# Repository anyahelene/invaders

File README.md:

# invaders
##### A hand-held retro console based on the ATmega328P chip

## Features
* [ATmega328P](https://www.microchip.com/wwwproducts/en/ATMEGA328P) as the CPU, with
   * 16 MHz clock
   * 32 KiB flash memory for programs
   * 2 KiB static ram
   * 1 KiB EEPROM
* Choice of one of three OLED displays:
   * 2.42" monochrome 128x64 OLED with SPI interface, e.g., [this one from DIYMORE](https://www.diymore.cc/collections/display-module/products/2-42-inch-12864-oled-display-module-iic-i2c-spi-serial-for-arduino-c51-stm32-green-white-blue-yellow)
   * 1.5" color 128x128 OLED with SPI interface, e.g., [this one from Waveshare](https://www.waveshare.com/1.5inch-RGB-OLED-Module.htm)
   * 1.3" monochrome 128x64 OLED with I2C interface, found as infinite clones such as [this one from Luxorparts](https://www.kjell.com/no/produkter/elektro-og-verktoy/elektronikk/optokomponenter/led-lcd-skjermer/luxorparts-grafisk-oled-skjerm-128-x-64-piksler-1-3--p87946)
   * The board has pin headers and mounting holes for these three displays, but other display sizes might fit, and different pinouts might be accommodated by wires
   * The above displays are available from Ebay ($2.50 for a small display, up to ~$18 for large/color), and similar displays can be found at [Adafruit](https://adafruit.com/), [Sparkfun](https://sparkfun.com/) or your local electronics store
* Four directional buttons on the left-hand side
* [Thumbstick (PSP1000 replacement)](https://www.adafruit.com/product/444) *or* two buttons on the right-hand side
* Two trigger buttons on the top edge
* Reset button on the bottom side
* Space for 2xAAA batteries + also a JST-PH battery connector (as seen on the micro:bit)
* Micro USB power connector
* 6 pin AVR ICSP header for programming
* Space for a tiny speaker/buzzer
* Power led + two controllable leds
* Four M2 mounting holes

## (Soft|Firm)ware
* TBD

## Circuit board
* [KiCad](http://www.kicad-pcb.org/) files for the board can be found in the [pcb/](pcb/) subdirectory.
* You also need the symbols and footprints from https://github.com/anyahelene/a-symbols
* Alternatively, the board can be manufactured directly from the Gerber files in [pcb/fab/](pcb/fab/).
* An [interactive BOM](https://htmlpreview.github.io/?https://github.com/anyahelene/invaders/blob/master/pcb/bom/ibom.html) is available in [pcb/bom/](pcb/bom/)

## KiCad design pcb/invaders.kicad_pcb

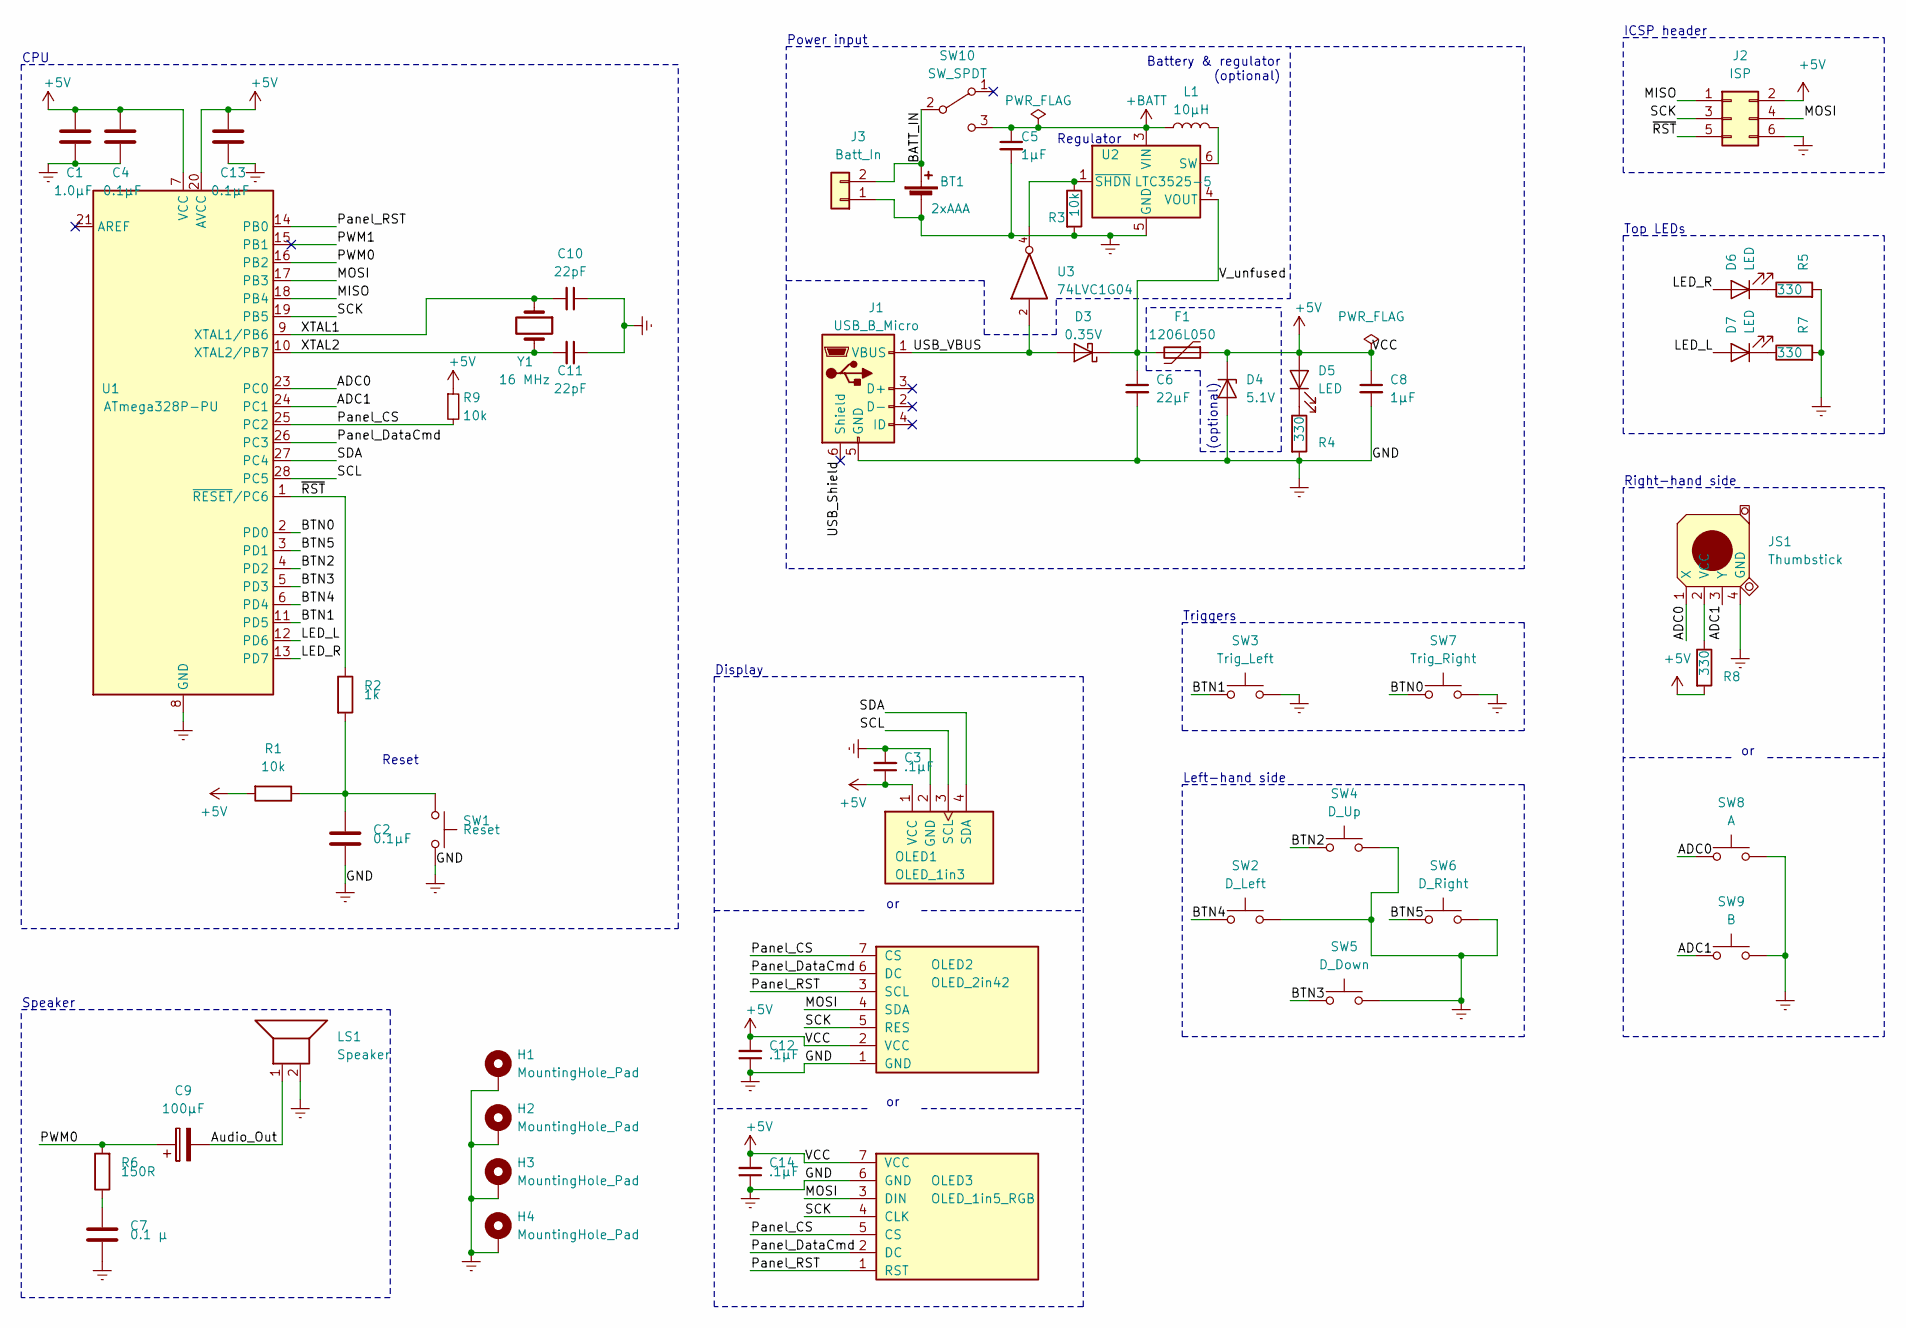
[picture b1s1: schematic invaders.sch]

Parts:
BT1: 2xAAA; BatteryHolder_Keystone_2468_2xAAA; Part Keystone 2468
C1: 1.0µF; C_1206_3216Metric_Pad1.42x1.75mm_HandSolder
C2, C4, C13: 0.1µF; C_0805_2012Metric_Pad1.15x1.40mm_HandSolder
C3, C12, C14: .1µF; C_0805_2012Metric_Pad1.15x1.40mm_HandSolder
C5, C8: 1µF; C_1206_3216Metric_Pad1.42x1.75mm_HandSolder
C6: 22µF; C_1206_3216Metric_Pad1.42x1.75mm_HandSolder; Part Taiyo LMK316ABJ226ML-T
C7: 0.1 µ; C_0805_2012Metric_Pad1.15x1.40mm_HandSolder
C9: 100µF; CP_Radial_D6.3mm_P2.50mm
C10, C11: 22pF; C_0805_2012Metric_Pad1.15x1.40mm_HandSolder
D3: 0.35V; D_SOD-123F; Part Rohm RSX101MM-30TR
D4: 5.1V; D_DO-41_SOD81_P7.62mm_Horizontal; Part RND 1N4733A
D5, D6, D7: LED; LED_1206_3216Metric_Pad1.42x1.75mm_HandSolder
F1: 1206L050; Fuse_1206_3216Metric_Pad1.42x1.75mm_HandSolder
H1, H2, H3, H4: MountingHole_Pad; MountingHole_2.2mm_M2_Pad_Via
J1: USB_B_Micro; USB_Micro-B_Molex-105017-0001; Part Molex 105017
J2: ISP; PinHeader_2x03_P2.54mm_Vertical
J3: Batt_In; JST_PH_S2B-PH-K_1x02_P2.00mm_Horizontal
JS1: Thumbstick; psp_thumbstick; Part PSP1000 thumbstick
L1: 10µH; L_1210_3225Metric_Pad1.42x2.65mm_HandSolder; Part Murata DFE322512C 1277A
LS1: Speaker; Buzzer_12x9.5RM7.6
OLED1: OLED_1in3; OLED_1in3_i2c
OLED2: OLED_2in42; OLED_2in42_spi_i2c
OLED3: OLED_1in5_RGB; OLED_1in5_spi_rgb
R1, R3, R9: 10k; R_1206_3216Metric_Pad1.42x1.75mm_HandSolder
R2: 1k; R_1206_3216Metric_Pad1.42x1.75mm_HandSolder
R4, R5, R7, R8: 330; R_1206_3216Metric_Pad1.42x1.75mm_HandSolder
R6: 150R; R_1206_3216Metric_Pad1.42x1.75mm_HandSolder
SW1: Reset; SW_PUSH_6mm; Part 6x6mm tactile, e.g. ALPS SKHHAMA010
SW2: D_Left; SW_PUSH_6mm; Part 6x6mm tactile, e.g. ALPS SKHHAMA010
SW3: Trig_Left; SW_Tactile_SPST_Angled_PTS645Vx58-2LFS; Part 6mm angled tactile, e.g. C&K PTS645VM58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
SW4: D_Up; SW_PUSH_6mm; Part 6x6mm tactile, e.g. ALPS SKHHAMA010
SW5: D_Down; SW_PUSH_6mm; Part 6x6mm tactile, e.g. ALPS SKHHAMA010
SW6: D_Right; SW_PUSH_6mm; Part 6x6mm tactile, e.g. ALPS SKHHAMA010
SW7: Trig_Right; SW_Tactile_SPST_Angled_PTS645Vx58-2LFS; Part 6mm angled tactile, e.g. C&K PTS645VM58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
SW8: A; SW_PUSH_6mm; Part 6x6mm tactile, e.g. ALPS SKHHAMA010
SW9: B; SW_PUSH_6mm; Part 6x6mm tactile, e.g. ALPS SKHHAMA010
SW10: SW_SPDT; SW_E-Switch_EG1224_SPDT_Angled
U1: ATmega328P-PU; DIP-28_W7.62mm_Socket
U2: LTC3525-5; SOT-363_SC-70-6
U3: 74LVC1G04; SOT-23-5_HandSoldering
Y1: 16 MHz; Crystal_HC49-4H_Vertical

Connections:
+5V: C1.1, C3.1, C4.1, C8.1, C12.2, C13.1, C14.2, D4.1 (K), D5.2 (A), F1.1, J2.2, OLED1.1 (VCC), OLED2.2 (VCC), OLED3.7 (VCC), R1.2, R8.2, R9.1, U1.7 (VCC), U1.20 (AVCC), U3.5 (VCC)
+BATT: C5.1, L1.1, SW10.3 (C), U2.3 (VIN)
/ADC0: JS1.1 (X), SW8.1, U1.23 (PC0)
/ADC1: JS1.3 (Y), SW9.1, U1.24 (PC1)
/Audio_Out: C9.2, LS1.1
/BATT_IN: BT1.1 (+), J3.2, SW10.2 (B)
/BTN0: SW7.1, U1.2 (PD0)
/BTN1: SW3.1, U1.11 (PD5)
/BTN2: SW4.1, U1.4 (PD2)
/BTN3: SW5.1, U1.5 (PD3)
/BTN4: SW2.1, U1.6 (PD4)
/BTN5: SW6.1, U1.3 (PD1)
/LED_L: D7.2 (A), U1.12 (PD6)
/LED_R: D6.2 (A), U1.13 (PD7)
/MISO: J2.1, U1.18 (PB4)
/MOSI: J2.4, OLED2.4 (SDA), OLED3.3 (DIN), U1.17 (PB3)
/PWM0: C9.1, R6.2, U1.16 (PB2)
/Panel_CS: OLED2.7 (CS), OLED3.5 (CS), R9.2, U1.25 (PC2)
/Panel_DataCmd: OLED2.6 (DC), OLED3.2 (DC), U1.26 (PC3)
/Panel_RST: OLED2.3 (SCL), OLED3.1 (RST), U1.14 (PB0)
/SCK: J2.3, OLED2.5 (RES), OLED3.4 (CLK), U1.19 (PB5)
/SCL: OLED1.3 (SCL), U1.28 (PC5)
/SDA: OLED1.4 (SDA), U1.27 (PC4)
/USB_Shield: J1.6 (Shield)
/USB_VBUS: D3.2 (A), J1.1 (VBUS), U3.2
/V_unfused: C6.1, D3.1 (K), F1.2, U2.4 (VOUT)
/XTAL1: C10.2, U1.9 (XTAL1/PB6), Y1.1
/XTAL2: C11.2, U1.10 (XTAL2/PB7), Y1.2
/~RST: J2.5, R2.1, U1.1 (~RESET~/PC6)
Earth: BT1.2 (-), C1.2, C2.1, C3.2, C4.2, C5.2, C6.2, C7.1, C8.2, C10.1, C11.1, C12.1, C13.2, C14.1, D4.2 (A), H1.1, H2.1, H3.1, H4.1, J1.5 (GND), J2.6, J3.1, JS1.4 (GND), LS1.2, OLED1.2 (GND), OLED2.1 (GND), OLED3.6 (GND), R3.2, R4.2, R5.2, R7.2, SW1.2, SW2.2, SW3.2, SW4.2, SW5.2, SW6.2, SW7.2, SW8.2, SW9.2, U1.8 (GND), U1.22 (GND), U2.2 (GND), U2.5 (GND), U3.3 (GND)
unnamed: C2.2, R1.1, R2.2, SW1.1
unnamed: C7.2, R6.1
unnamed: D5.1 (K), R4.1
unnamed: D6.1 (K), R5.1
unnamed: D7.1 (K), R7.1
unnamed: JS1.2 (VCC), R8.1
unnamed: L1.2, U2.6 (SW)
unnamed: R3.1, U2.1 (~SHDN), U3.4

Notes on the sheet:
Regulator
Right-hand side
Triggers
Left-hand side
Display
Reset
CPU
Top LEDs
ICSP header
(optional)
Battery & regulator (optional)
Power input
Speaker

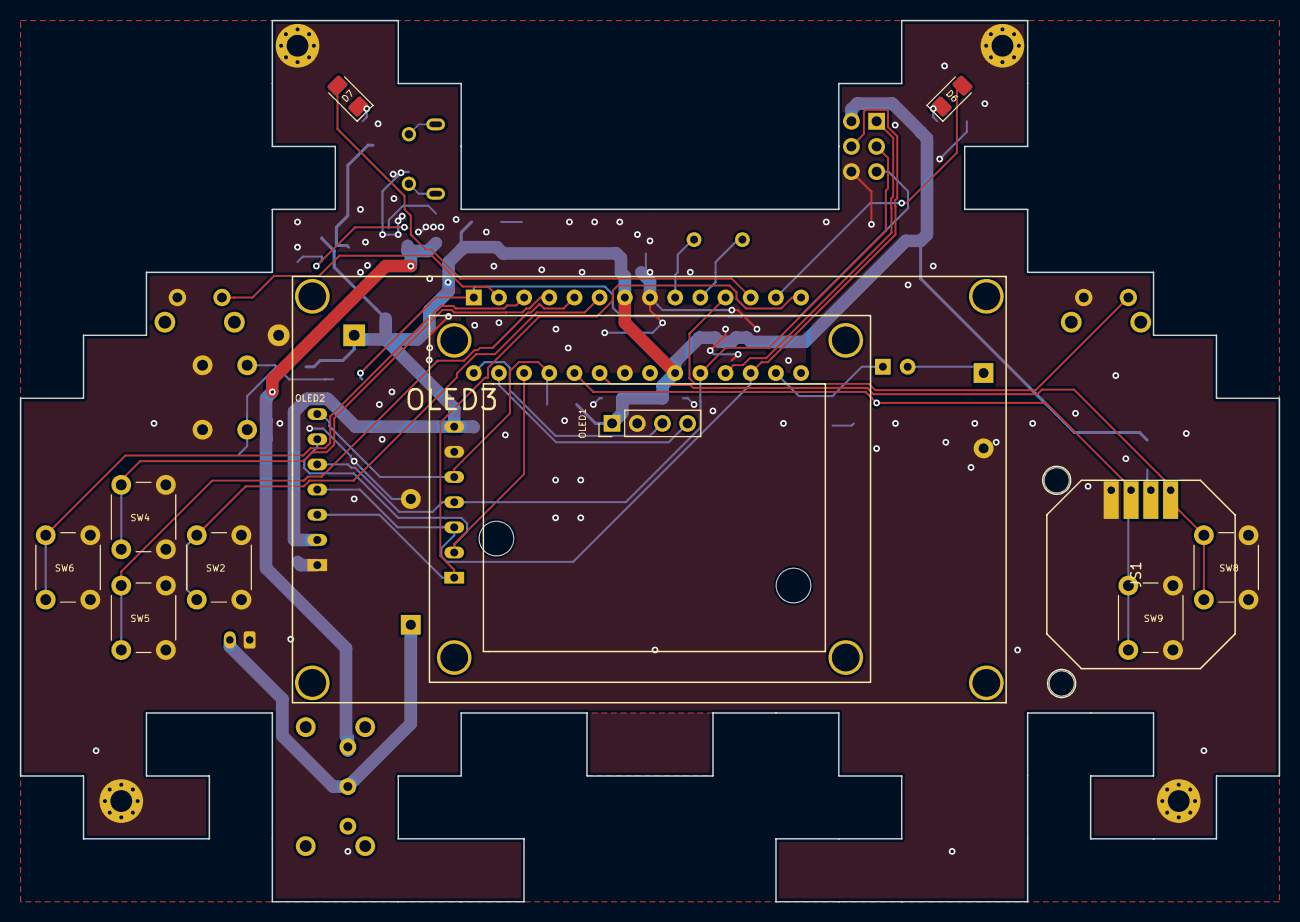
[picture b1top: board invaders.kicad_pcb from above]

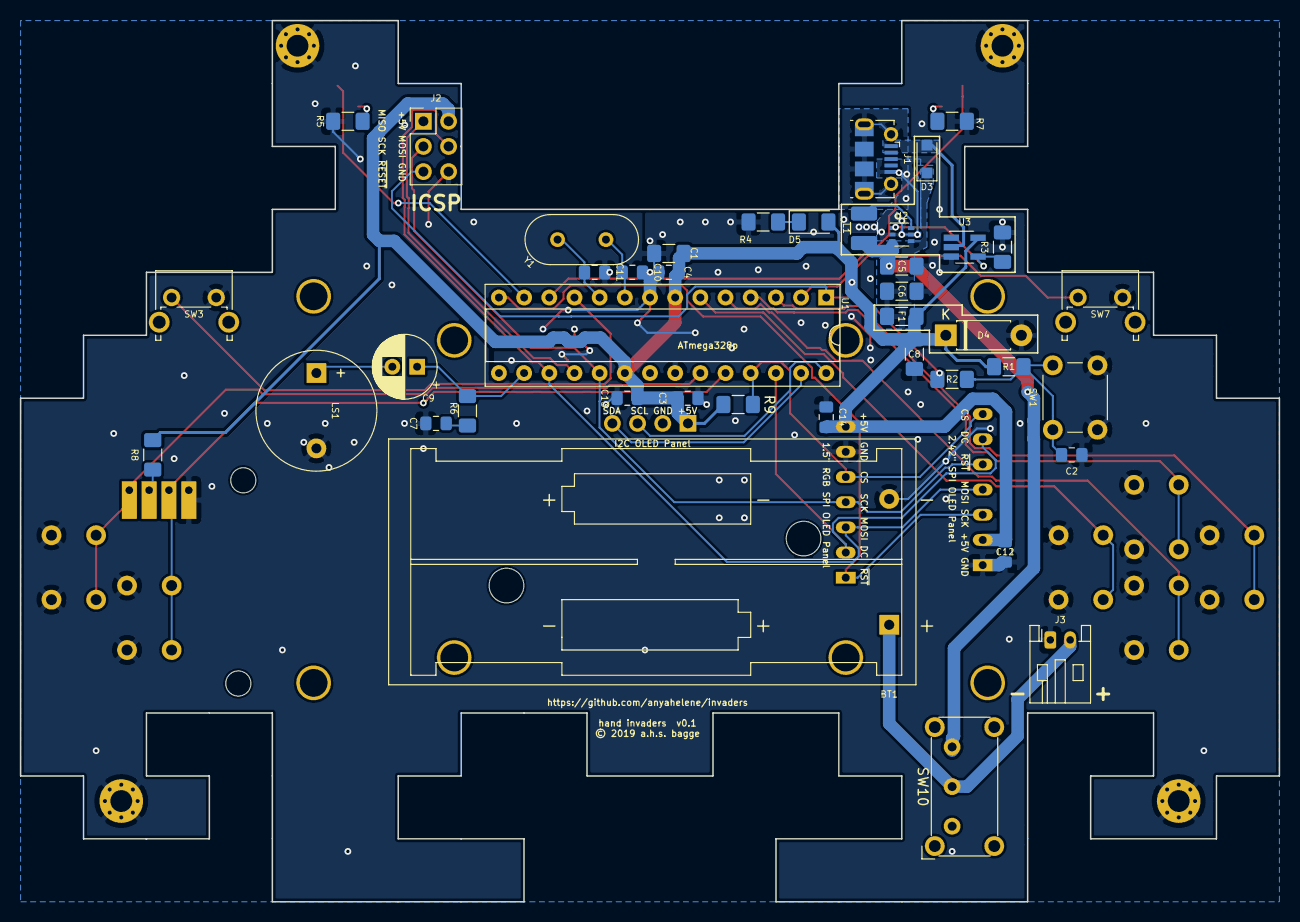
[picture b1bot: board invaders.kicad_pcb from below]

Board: 2 copper layers, 127.0 x 88.9 mm, 57 parts (41 on the bottom side), 37 nets.

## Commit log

2019-06-24 v0.1
2019-06-24 library fixes
2019-06-24 3d model shot
2019-06-24 cleanup; add pullup to Panel_CS

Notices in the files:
pcb/invaders.kicad_pcb:
© 2019 a.h.s. bagge
